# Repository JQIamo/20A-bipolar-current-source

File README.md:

# Bias Coils Current Controller
This repo provides information regarding the Bias Coils Current Controller (here on out referred to as “the controller”) used by the Schine Group at the Joint Quantum Institute (JQI) at University of Maryland, College Park. This is an experimental apparatus designed to drive Helmholtz coil pairs to cancel external magnetic fields which would otherwise disturb the experiment. The controller provides an output current proportional to an input voltage and features an ultra-low noise feedback circuit design for precise control of the output current down to the fractional mA level. The controller has three channels to independently control the magnetic fields along the x, y, and z axes.

## 20A-bipolar-current-source
This project is based on the [`20A-bipolar-current-source`](https://github.com/JQIamo/20A-bipolar-current-source/tree/faf83a785aa46d90d6e65fa55f9879bae6bd2d8a) design of Mingshu Zhao and Alessandro Restelli. Details on the circuit can be found in their [research article in AIP Advances](https://doi.org/10.1063/5.0138145).

## Circuit files
There are several KiCad project folders within the `kicad` directory in this repo.
* `controller_board` contains the circuit board for the main controller board on which the analog PI feedback is located.
* `Controller_supply` contains the controller's on-board power supply circuit board (used for powering the controller boards)
* `H-bridge` is for the development of the MOT coil current controller (empty project as of Jun 06, 2024).
* `rear` contains the original, liquid-cooled circuit board design housing the power MOSFETs that control the coil current. (Not used in this controller)
* `SchineLab_CoilFET_Board` contains the modified, air-cooled circuit board design housing the power MOSFETs for coil current control. (Used in this controller)

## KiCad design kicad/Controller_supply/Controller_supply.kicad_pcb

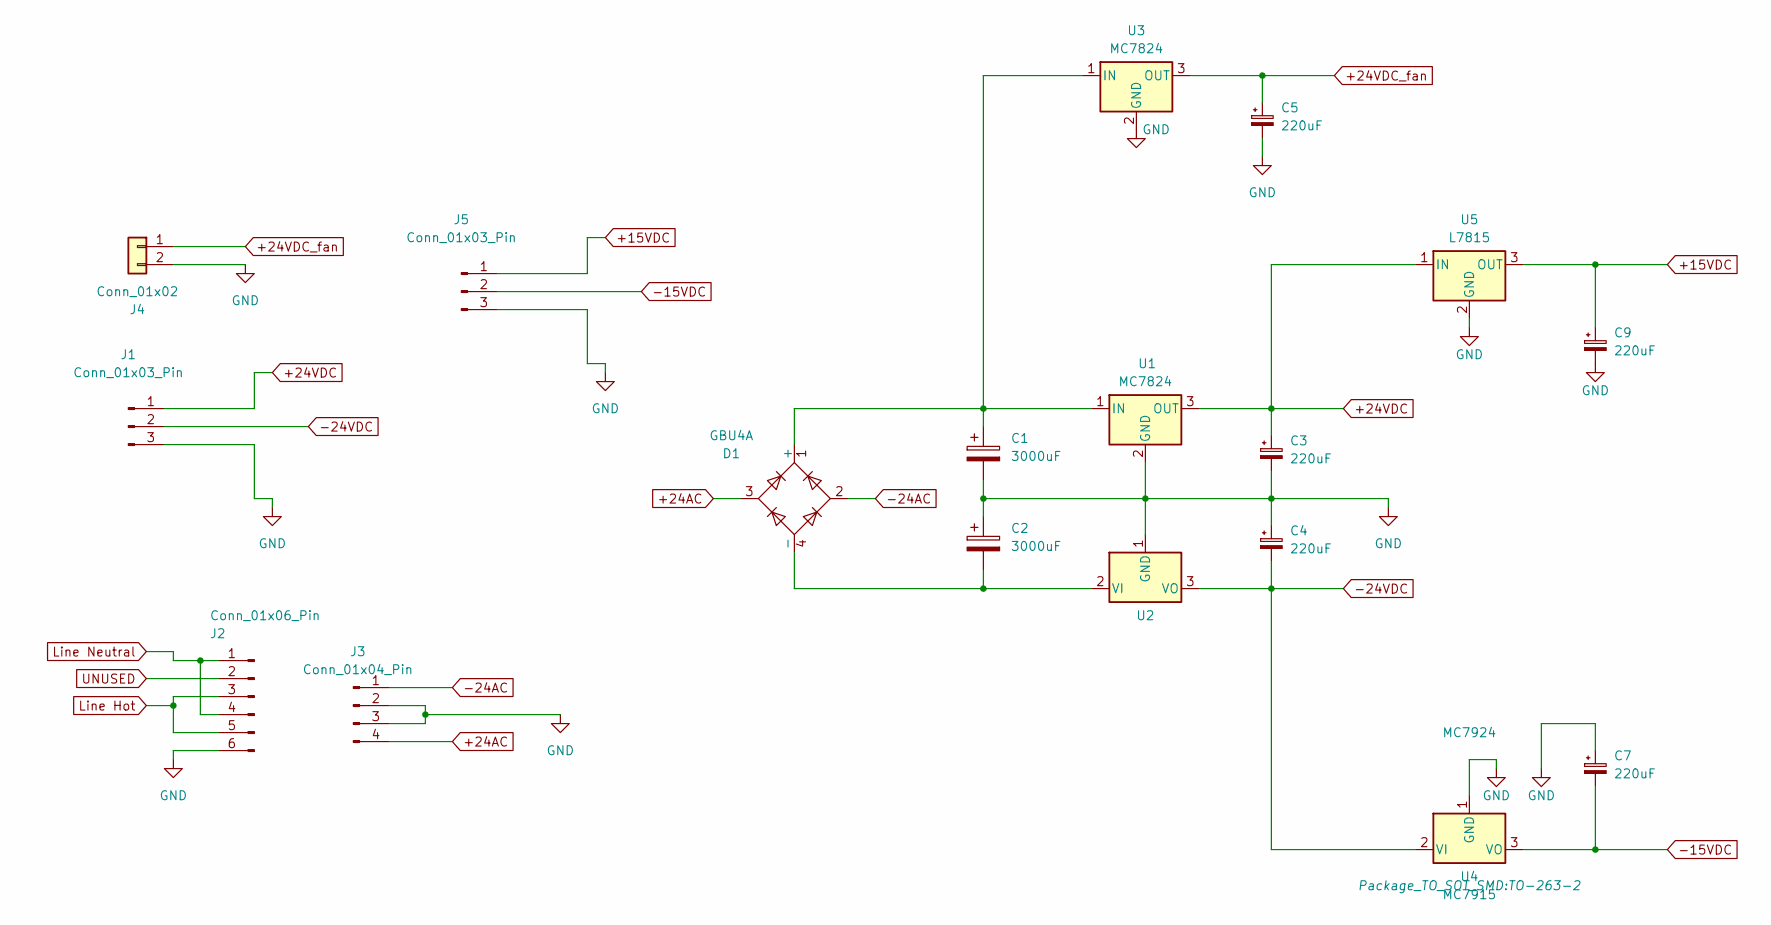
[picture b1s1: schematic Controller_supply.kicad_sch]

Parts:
C1, C2: 3000uF; CP_Elec_18x22; MPN EEE-FK1V302SV; DIGIKEY PARTNO P122523CT-ND
C3, C4, C5, C7, C9: 220uF; CP_Elec_10x10.5; MPN EEE-FK1H221P; DIGIKEY PARTNO PCE3812CT-ND
D1: GBU4A; Diode_Bridge_Vishay_GBU; MPN GBU4A; DIGIKEY PARTNO GBU4A-ND
J1, J5: Conn_01x03_Pin; PhoenixContact_GMSTBA_2,5_3-G-7,62_1x03_P7.62mm_Horizontal
J2: Conn_01x06_Pin
J3: Conn_01x04_Pin; Generic_pin-to-housing_1x04_P5.00mm_Horizontal
J4: Conn_01x02; Generic_7x7.5mm-footprt_1x02_P3.50mm_Horizontal
U1, U3: MC7824; TO-263-2; MPN MC7824CD2TR4G; DIGIKEY PARTNO MC7824CD2TR4GOSCT-ND
U2: MC7924; TO-263-2; MPN MC7924CD2TG; DIGIKEY PARTNO MC7924CD2TG-ND
U4: MC7915; TO-263-2
U5: L7815; TO-263-2

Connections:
+15VDC: C9.1, J5.1, U5.3 (OUT)
+24AC: D1.3, J3.4
+24VDC: C3.1, J1.1, U1.3 (OUT), U5.1 (IN)
+24VDC_fan: C5.1, J4.1, U3.3 (OUT)
-15VDC: C7.2, J5.2, U4.3 (VO)
-24AC: D1.2, J3.1
-24VDC: C4.2, J1.2, U2.3 (VO), U4.2 (VI)
GND: C1.2, C2.1, C3.2, C4.1, C5.2, C7.1, C9.2, J1.3, J2.6, J3.2, J3.3, J4.2, J5.3, U1.2 (GND), U2.1 (GND), U3.2 (GND), U4.1 (GND), U5.2 (GND)
unnamed: C1.1, D1.1 (+), U1.1 (IN), U3.1 (IN)
unnamed: C2.2, D1.4 (-), U2.2 (VI)
unnamed: J2.1, J2.4
unnamed: J2.3, J2.5

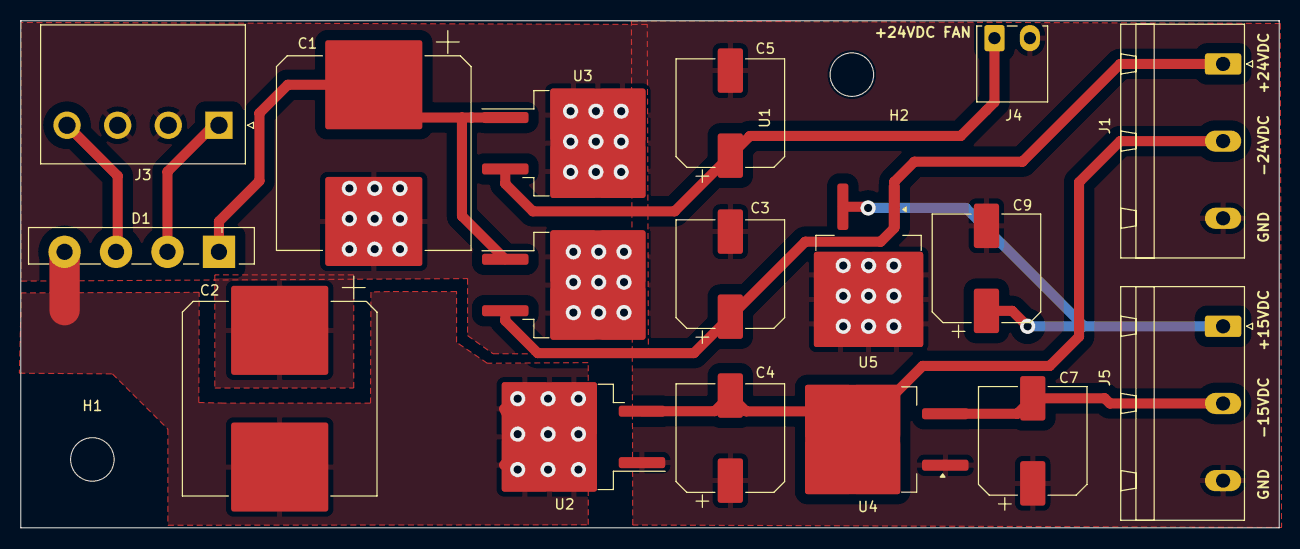
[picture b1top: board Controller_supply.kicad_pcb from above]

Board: 2 copper layers, 124.3 x 50.1 mm, 19 parts (0 on the bottom side), 10 nets.

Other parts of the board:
H1, H2: MountingHole_4.3mm_M4

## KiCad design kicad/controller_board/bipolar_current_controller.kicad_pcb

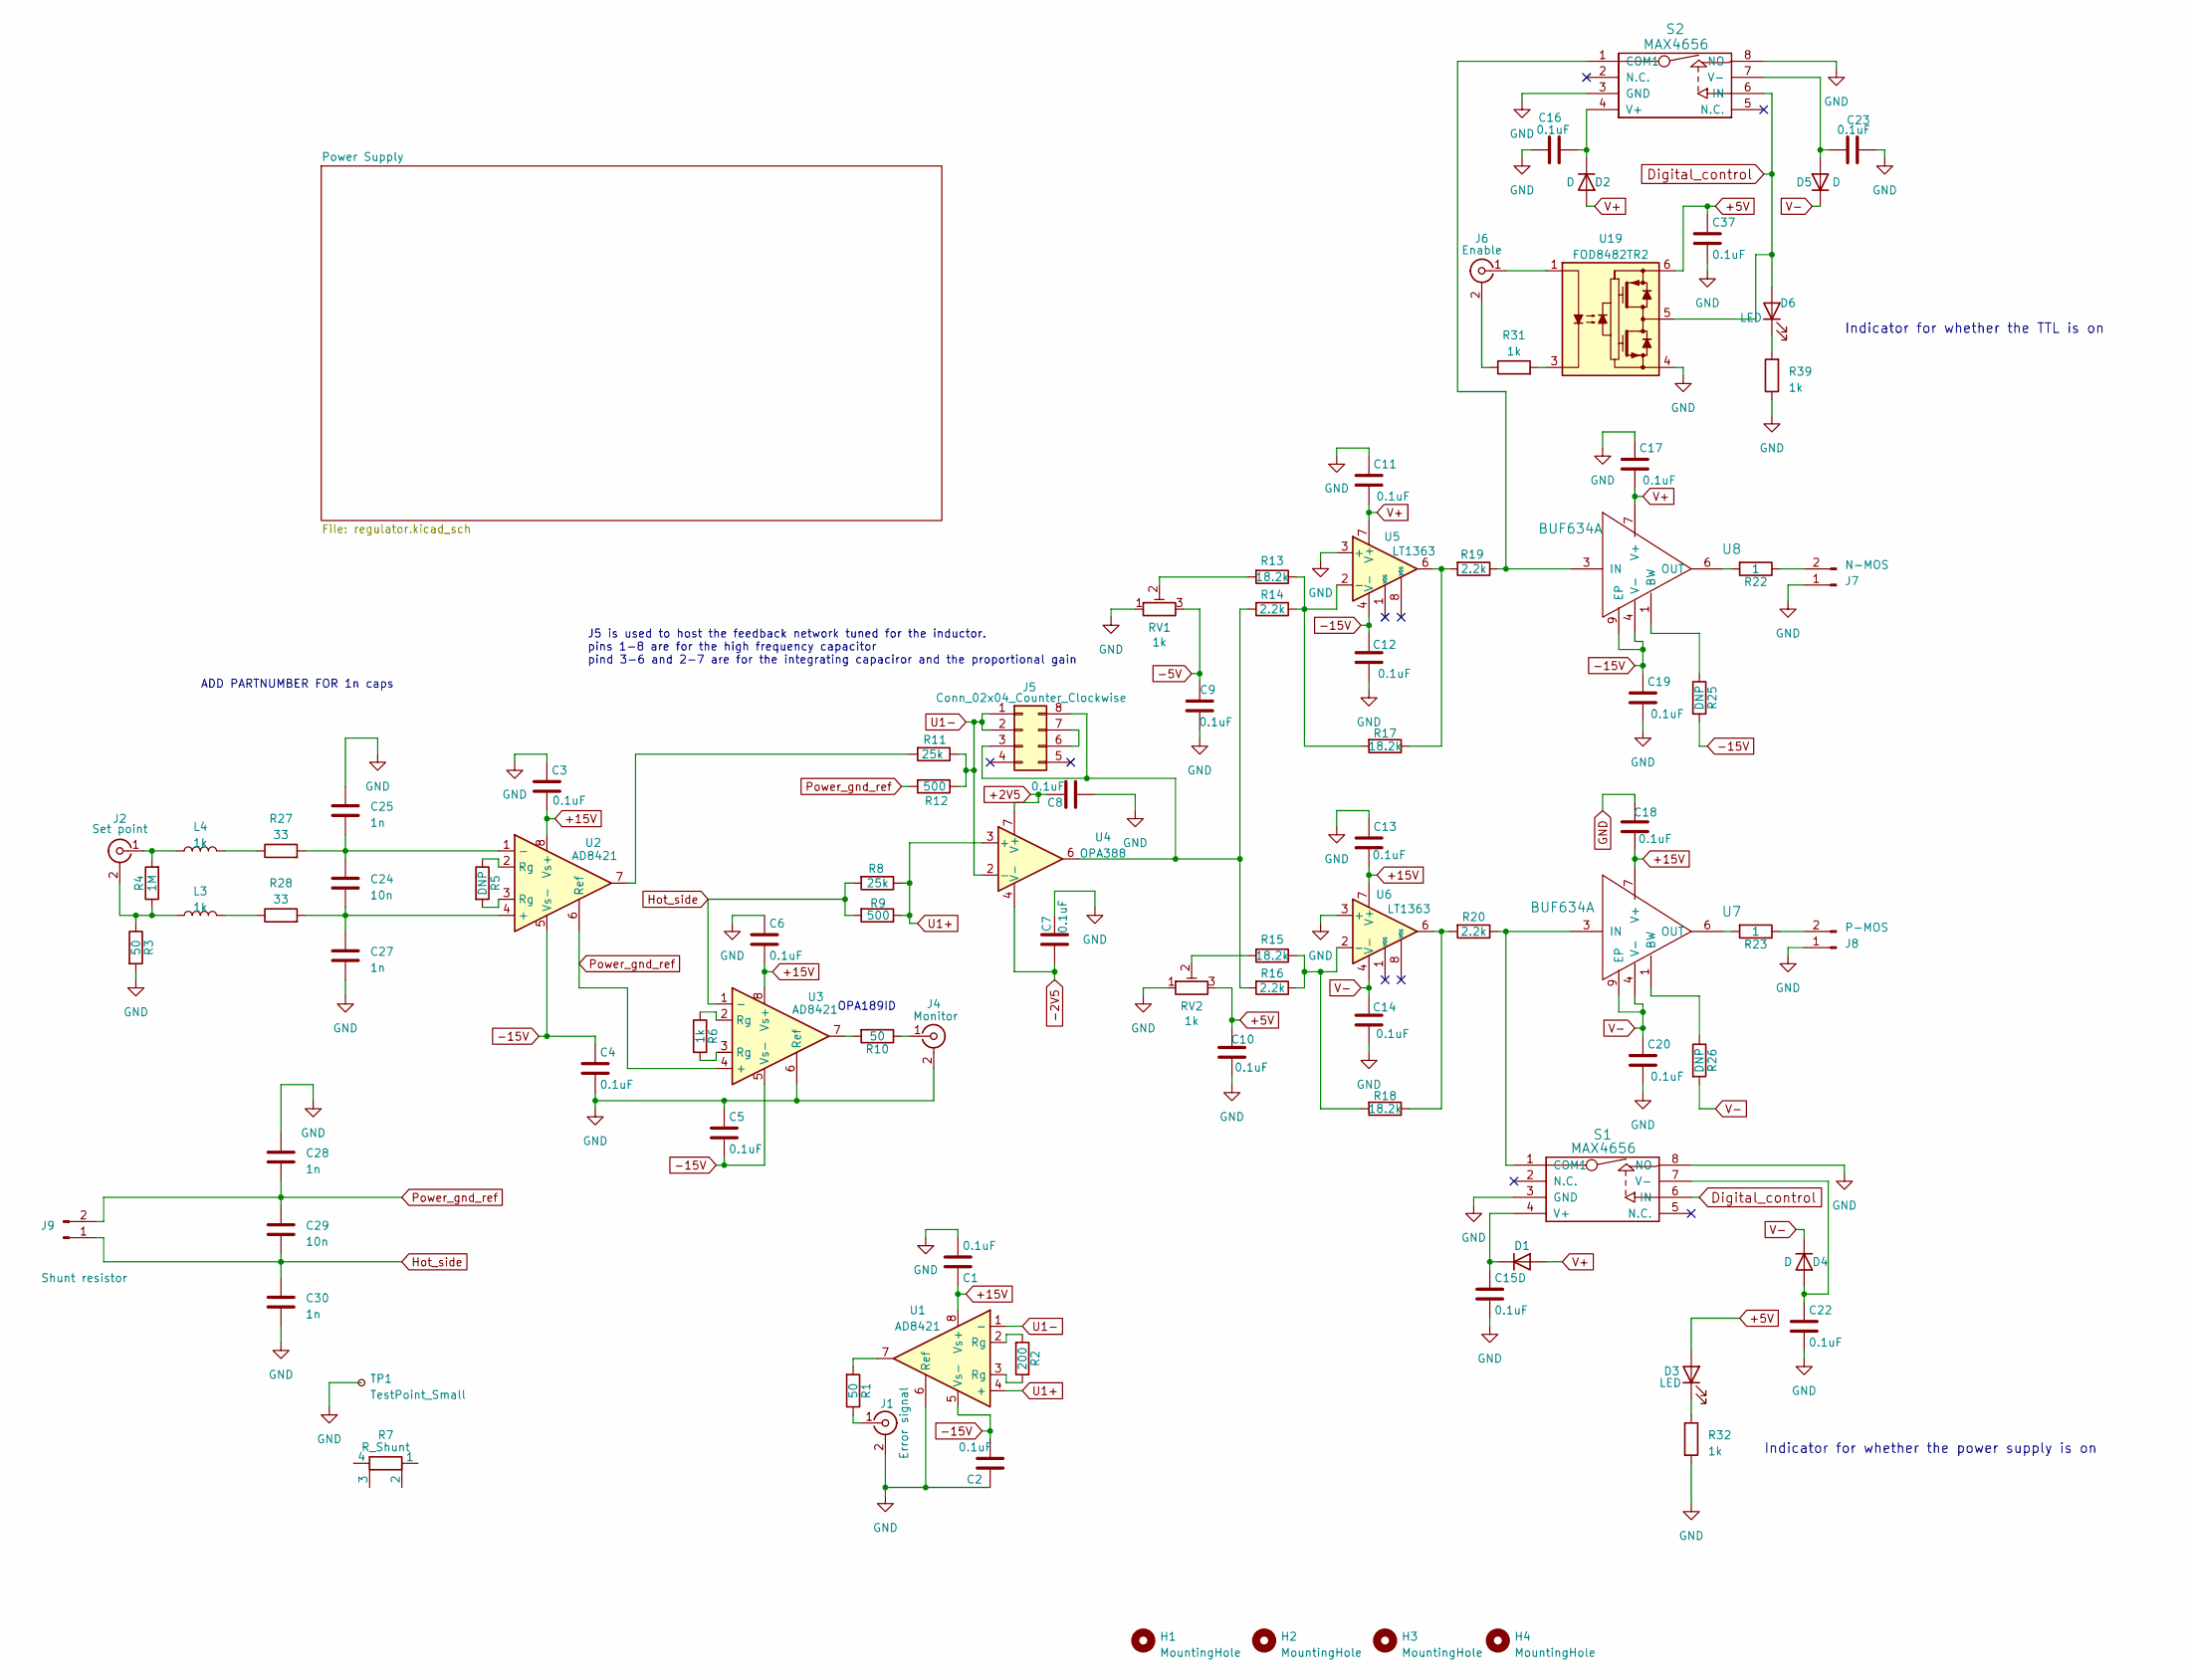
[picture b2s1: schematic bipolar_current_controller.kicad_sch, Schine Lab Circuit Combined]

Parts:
C1, C2, C3, C4, C5, C6, C7, C8, C9, C10, C11, C12, C13, C14, C15, C16, C17, C18, C19, C20, C22, C23, C37: 0.1uF; C_0603_1608Metric; MPN GCM188R71H104JA57D; DIGIKEY PARTNO 490-14357-1-ND
C24, C29: 10n; C_0603_1608Metric; MPN PARTNO C1608C0G1H103J080AA; DIGIKEY PARTNO 445-7404-1-ND
C25, C27, C28, C30: 1n; C_0603_1608Metric; MPN 1276-1018-1-ND; DIGIKEY PARTNO 1276-1018-1-ND
D1, D2, D4, D5: D; D_MiniMELF; MPN CLL4150 TR PBFREE; DIGIKEY PARTNO 1514-CLL4150TRPBFREECT-ND
D3, D6: LED; LED_D5.0mm_Horizontal_O3.81mm_Z3.0mm; MPN HLMP-4700-C0002; DIGIKEY PARTNO 516-2483-1-ND
H1, H2, H3, H4: MountingHole; MountingHole_4mm
J1: Error signal; BNC_Amphenol_B6252HB-NPP3G-50_Horizontal_mount_float; MPN 5227161-7; DIGIKEY PARTNO A32260-ND
J2: Set point; BNC_Amphenol_B6252HB-NPP3G-50_Horizontal_mount_float; MPN 5227161-7; DIGIKEY PARTNO A32260-ND
J4: Monitor; BNC_Amphenol_B6252HB-NPP3G-50_Horizontal_mount_float; MPN 5227161-7; DIGIKEY PARTNO A32260-ND
J5: Conn_02x04_Counter_Clockwise; SSO-8_7.62x10.1mm_P2.54mm_Clearance8mm; MPN 114-87-308-41-134161; DIGIKEY PARTNO 1212-1032-ND
J6: Enable; BNC_Amphenol_B6252HB-NPP3G-50_Horizontal_mount_float; MPN 5227161-7; DIGIKEY PARTNO A32260-ND
J7: N-MOS; Molex_KK-254_AE-6410-02A_1x02_P2.54mm_Vertical
J8: P-MOS; Molex_KK-254_AE-6410-02A_1x02_P2.54mm_Vertical
J9: Shunt resistor; Molex_KK-254_AE-6410-02A_1x02_P2.54mm_Vertical
L3, L4: 1k; L_0603_1608Metric; MPN MMZ1608R102ATA00; DIGIKEY PARTNO 445-MMZ1608R102ATA00CT-ND
R1, R3, R10: 50; R_0603_1608Metric; MPN FC0603E50R0BTBST1; DIGIKEY PARTNO 764-FC0603E50R0BTBST1CT-ND
R2: 200; R_0603_1608Metric; MPN RNCF0603TKY200R; DIGIKEY PARTNO RNCF0603TKY200RCT-ND
R4: 1M; R_0603_1608Metric; MPN RT0603BRD071ML; DIGIKEY PARTNO YAG4498CT-ND
R5: DNP; R_0805_2012Metric
R6: 1k; R_0805_2012Metric; MPN RNCF0805TKY1K00; DIGIKEY PARTNO RG2012V1.0KPCT-ND
R7: R_Shunt; MPN Y09430R01000F9L; DIGIKEY PARTNO 804-1050-ND
R8, R11: 25k; R_2512_6332Metric; MPN Y174525K0000T9R; DIGIKEY PARTNO 804-1122-1-ND
R9, R12: 500; R_2512_6332Metric; MPN Y1121500R000T9R; DIGIKEY PARTNO Y1121-500CT-ND
R13, R15, R17, R18: 18.2k; R_0805_2012Metric; MPN RK73H2ATTD1822F; DIGIKEY PARTNO 2019-RK73H2ATTD1822FCT-ND
R14, R16, R19, R20: 2.2k; R_0805_2012Metric; MPN MCU08050C2201FP500; DIGIKEY PARTNO 749-1728-1-ND
R22, R23: 1; R_0603_1608Metric; MPN RNCP0603FTD1R00; DIGIKEY PARTNO RNCP0603FTD1R00CT-ND
R25, R26: DNP; R_0603_1608Metric
R27, R28: 33; R_0603_1608Metric; MPN RC0603FR-0733RL; DIGIKEY PARTNO 311-33.0HRCT-ND
R31, R32, R39: 1k; R_0603_1608Metric; MPN RNCP0603FTD1K00; DIGIKEY PARTNO RNCP0603FTD1K00CT-ND
RV1, RV2: 1k; Potentiometer_Bourns_3296W_Vertical; MPN 3296W-1-102LF; DIGIKEY PARTNO 3296W-102LF-ND
S1, S2: MAX4656; MAX4656ESA+; MPN MAX4656ESA+; DIGIKEY PARTNO MAX4656ESA+-ND
TP1: TestPoint_Small; Laird_Technologies_BMI-S-210-F_44.00x30.50mm; MPN BMI-S-210-F and BMI-S-210-C; DIGIKEY PARTNO 903-1057-1-ND and 903-1020-ND
U1, U2, U3: AD8421; AD8421ARZ-R7; MPN AD8421ARZ-R7; DIGIKEY PARTNO AD8421ARZ-R7CT-ND
U4: OPA388; OPA388IDR; Partno MPN; DIGIKEY PARTNO 296-45348-1-ND
U5, U6: LT1363; LT1363CS8#TRPBF; MPN LT1363CS8#TRPBF; DIGIKEY PARTNO 505-LT1363CS8#TRPBFCT-ND
U7, U8: BUF634A; TI_SO-PowerPAD-8_ThermalVias; MPN BUF634AIDDAR; DIGIKEY PARTNO 296-BUF634AIDDARCT-ND
U19: FOD8482TR2; SSO-6_6.8x4.6mm_P1.27mm_Clearance8mm; MPN FOD8482TR2; DIGIKEY PARTNO 488-FOD8482TR2CT-ND

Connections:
+2V5: C8.2, U4.7 (V+); also elsewhere on the board
+5V: C10.2, C37.1, D3.2 (A), RV2.3, U19.6 (VCC); also elsewhere on the board
+15V: C1.1, C3.2, C6.2, C13.2, C18.2, U1.8 (Vs+), U2.8 (Vs+), U3.8 (Vs+), U6.7 (V+), U7.7 (V+); also elsewhere on the board
-2V5: C7.1, U4.4 (V-); also elsewhere on the board
-5V: C9.1, RV1.3; also elsewhere on the board
-15V: C2.2, C4.1, C5.2, C12.2, C19.1, R25.2, U1.5 (Vs-), U2.5 (Vs-), U3.5 (Vs-), U5.4 (V-), U8.4 (V-), U8.9 (EP); also elsewhere on the board
Digital_control: D6.2 (A), S1.6 (IN), S2.6 (IN), U19.5 (VO)
GND: C1.2, C2.1, C3.1, C4.2, C5.1, C6.1, C7.2, C8.1, C9.2, C10.1, C11.1, C12.1, C13.1, C14.1, C15.2, C16.1, C17.1, C18.1, C19.2, C20.2, C22.2, C23.1, C25.1, C27.2, C28.1, C30.2, C37.2, J1.2 (Ext), J4.2 (Ext), J7.1, J8.1, R3.2, R32.2, R39.1, RV1.1, RV2.1, S1.3 (GND), S1.8 (NO), S2.3 (GND), S2.8 (NO), TP1.1, U1.6 (Ref), U3.6 (Ref), U5.3 (+), U6.3 (+), U19.4 (VEE); also elsewhere on the board
Hot_side: C29.2, C30.1, J9.1, R8.2, R9.2, U3.1 (-)
unnamed: C15.1, D1.1 (K), S1.4 (V+)
unnamed: C16.2, D2.1 (K), S2.4 (V+)
unnamed: D3.1 (K), R32.1
unnamed: C22.1, D4.2 (A), S1.7 (V-)
unnamed: C23.2, D5.2 (A), S2.7 (V-)
unnamed: D6.1 (K), R39.2
unnamed: J1.1 (In), R1.1
unnamed: J2.2 (Ext), L3.1, R3.1, R4.1
unnamed: J2.1 (In), L4.1, R4.2
unnamed: J4.1 (In), R10.1
unnamed: J5.3, J5.8, R14.2, R16.2, U4.6
unnamed: J5.6, J5.7
unnamed: J6.2 (Ext), R31.1
unnamed: J6.1 (In), U19.1 (A)
unnamed: J7.2, R22.1
unnamed: J8.2, R23.1
unnamed: L3.2, R28.1
unnamed: L4.2, R27.1
unnamed: R1.2, U1.7
unnamed: R2.1, U1.3 (Rg)
unnamed: R2.2, U1.2 (Rg)
unnamed: R5.1, U2.2 (Rg)
unnamed: R5.2, U2.3 (Rg)
unnamed: R6.1, U3.2 (Rg)
unnamed: R6.2, U3.3 (Rg)
unnamed: R10.2, U3.7
unnamed: R11.2, U2.7
unnamed: R13.2, RV1.2
unnamed: R15.2, RV2.2
unnamed: R17.1, R19.2, U5.6
unnamed: R18.1, R20.2, U6.6
unnamed: R20.1, S1.1 (COM1), U7.3 (IN)
unnamed: R19.1, S2.1 (COM1), U8.3 (IN)
unnamed: C24.2, C27.1, R28.2, U2.4 (+)
unnamed: C24.1, C25.2, R27.2, U2.1 (-)
unnamed: R13.1, R14.1, R17.2, U5.2 (-)
unnamed: R15.1, R16.1, R18.2, U6.2 (-)
unnamed: R26.1, U7.1 (BW)
unnamed: R23.2, U7.6 (OUT)
unnamed: R25.1, U8.1 (BW)
unnamed: R22.2, U8.6 (OUT)
unnamed: R31.2, U19.3 (C)
Power_gnd_ref: C28.2, C29.1, J9.2, R12.2, U2.6 (Ref), U3.4 (+)
U1+: R8.1, R9.1, U1.4 (+), U4.3 (+)
U1-: J5.1, J5.2, R11.1, R12.1, U1.1 (-), U4.2 (-)
V+: C11.2, C17.2, D1.2 (A), D2.2 (A), U5.7 (V+), U8.7 (V+); also elsewhere on the board
V-: C14.2, C20.1, D4.1 (K), D5.1 (K), R26.2, U6.4 (V-), U7.4 (V-), U7.9 (EP); also elsewhere on the board

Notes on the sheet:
J5 is used to host the feedback network tuned for the inductor. pins 1-8 are for the high frequency capacitor pind 3-6 and 2-7 are for the integrating capaciror and the proportional gain
ADD PARTNUMBER FOR 1n caps
Indicator for whether the TTL is on
Indicator for whether the power supply is on
OPA189ID

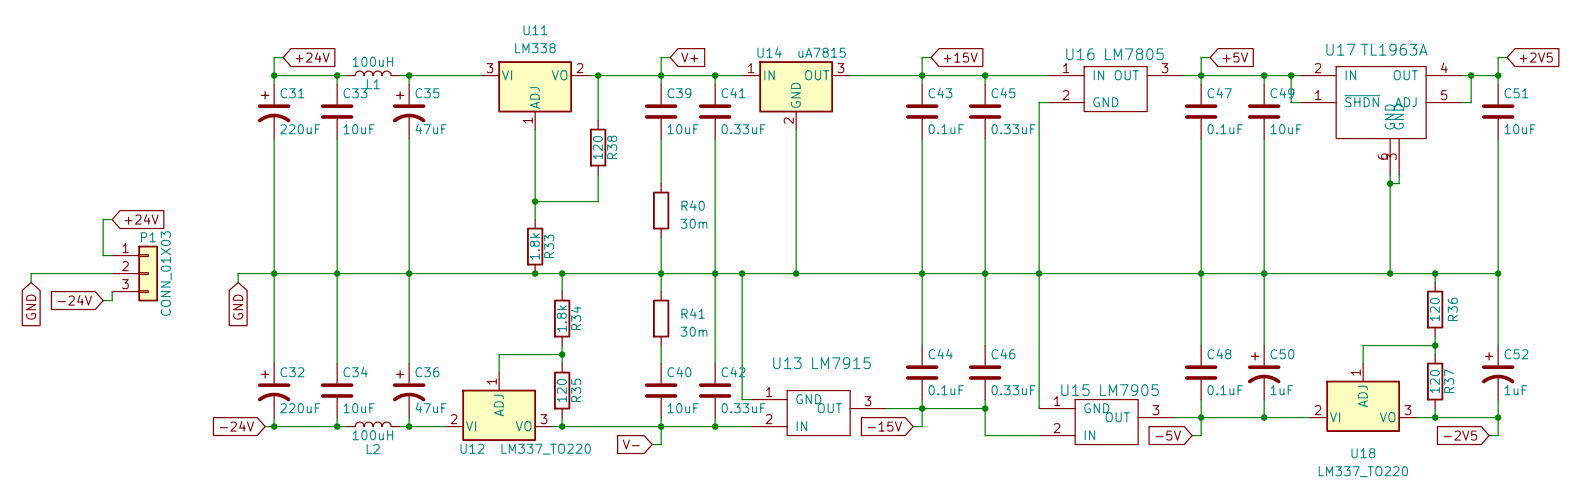
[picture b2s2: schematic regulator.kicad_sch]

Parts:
C31, C32: 220uF; CAP_polar_220uF; MPN EEE-FK1V221AP; DIGIKEY PARTNO PCE4428CT-ND
C33, C34, C39, C40, C49, C51: 10uF; C_1210_3225Metric; MPN C3225X7R1H106M250AC; DIGIKEY PARTNO 445-14933-1-ND
C35, C36: 47uF; CP_EIA-7343-43_Kemet-X; MPN T495X476K035ATE300; DIGIKEY PARTNO 399-3905-1-ND
C41, C42, C45, C46: 0.33uF; C_0603_1608Metric; MPN C1608X7R1H334K080AC; DIGIKEY PARTNO 445-5950-1-ND
C43, C44, C47, C48: 0.1uF; C_0603_1608Metric; MPN GCM188R71H104JA57D; DIGIKEY PARTNO 490-14357-1-ND
C50, C52: 1uF; CP_EIA-3528-21_Kemet-B; MPN T491B105K050AT; DIGIKEY PARTNO 399-9720-1-ND
L1, L2: 100uH; L_TDK_SLF10145; MPN SLF10145T-101M1R0-PF; DIGIKEY PARTNO 445-1976-1-ND
P1: CONN_01X03; Conn_01X03-3.5mm; MPN 1984620; DIGIKEY PARTNO 277-1722-ND
R33, R34: 1.8k; R_0603_1608Metric; MPN PTN0603E1801BST1; DIGIKEY PARTNO 764-1393-1-ND
R35, R36, R37, R38: 120; R_0603_1608Metric; MPN RG1608P-121-B-T5; DIGIKEY PARTNO RG16P120BCT-ND
R40, R41: 30m; R_1206_3216Metric; MPN D1WEL1206MR033F-T5; DIGIKEY PARTNO 4463-D1WEL1206MR033F-T5CT-ND
U11: LM338; TO-220-3_Vertical; MPN LM338T/NOPB; DIGIKEY PARTNO LM338T/NOPB-ND
U12: LM337_TO220; TO-220-3_Vertical; MPN LM337SP; DIGIKEY PARTNO 497-1585-5-ND
U13: LM7915; TO-263-2; MPN MC7915ACD2TG; DIGIKEY PARTNO MC7915ACD2TGOS-ND
U14: uA7815; TO-252-2; MPN BA7815FP-E2; DIGIKEY PARTNO BA7815FP-E2CT-ND
U15: LM7905; TO-263-2; MPN L7905CD2T-TR; DIGIKEY PARTNO 497-1214-1-ND
U16: LM7805; TO-263-3_TabPin2; MPN UA7805CKTTR; DIGIKEY PARTNO 296-20796-1-ND
U17: TL1963A; TL1963ADCQR; MPN TL1963ADCQR; DIGIKEY PARTNO 296-25119-1-ND
U18: LM337_TO220; TO-263-3_TabPin2; MPN LM337KTTR; DIGIKEY PARTNO 296-20746-1-ND

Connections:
+2V5: C51.1, U17.4 (OUT), U17.5 (ADJ); also elsewhere on the board
+5V: C47.1, C49.1, U16.3 (OUT), U17.1 (~SHDN), U17.2 (IN); also elsewhere on the board
+15V: C43.1, C45.1, U14.3 (OUT), U16.1 (IN); also elsewhere on the board
+24V: C31.1, C33.1, L1.1, P1.1
-2V5: C52.2, R37.2, U18.3 (VO); also elsewhere on the board
-5V: C48.2, C50.2, U15.3 (OUT), U18.2 (VI); also elsewhere on the board
-15V: C44.2, C46.2, U13.3 (OUT), U15.2 (IN); also elsewhere on the board
-24V: C32.2, C34.2, L2.1, P1.3
GND: C31.2, C32.1, C33.2, C34.1, C35.2, C36.1, C41.2, C42.1, C43.2, C44.1, C45.2, C46.1, C47.2, C48.1, C49.2, C50.1, C51.2, C52.1, P1.2, R33.2, R34.1, R36.1, R40.2, R41.1, U13.1 (GND), U14.2 (GND), U15.1 (GND), U16.2 (GND), U17.3 (GND), U17.6 (GND); also elsewhere on the board
unnamed: C39.2, R40.1
unnamed: C40.1, R41.2
unnamed: R33.1, R38.2, U11.1 (ADJ)
unnamed: C35.1, L1.2, U11.3 (VI)
unnamed: R34.2, R35.1, U12.1 (ADJ)
unnamed: C36.2, L2.2, U12.2 (VI)
unnamed: R36.2, R37.1, U18.1 (ADJ)
V+: C39.1, C41.1, R38.1, U11.2 (VO), U14.1 (IN); also elsewhere on the board
V-: C40.2, C42.2, R35.2, U12.3 (VO), U13.2 (IN); also elsewhere on the board

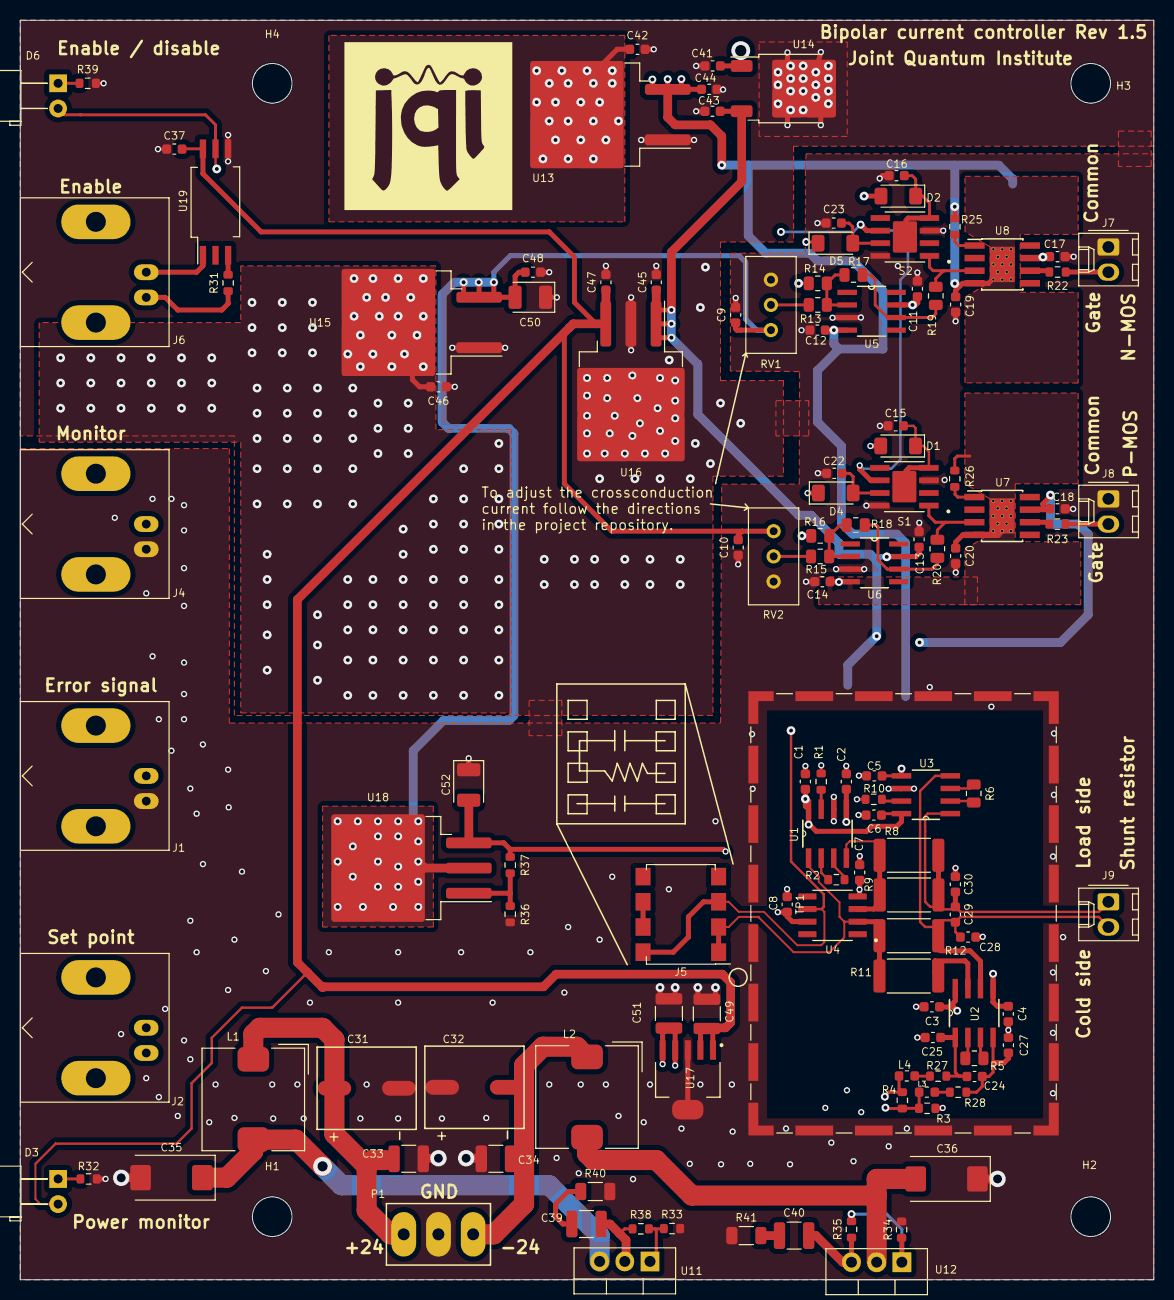
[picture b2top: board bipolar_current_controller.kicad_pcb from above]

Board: 4 copper layers, 114.3 x 127.0 mm, 130 parts (0 on the bottom side), 65 nets.

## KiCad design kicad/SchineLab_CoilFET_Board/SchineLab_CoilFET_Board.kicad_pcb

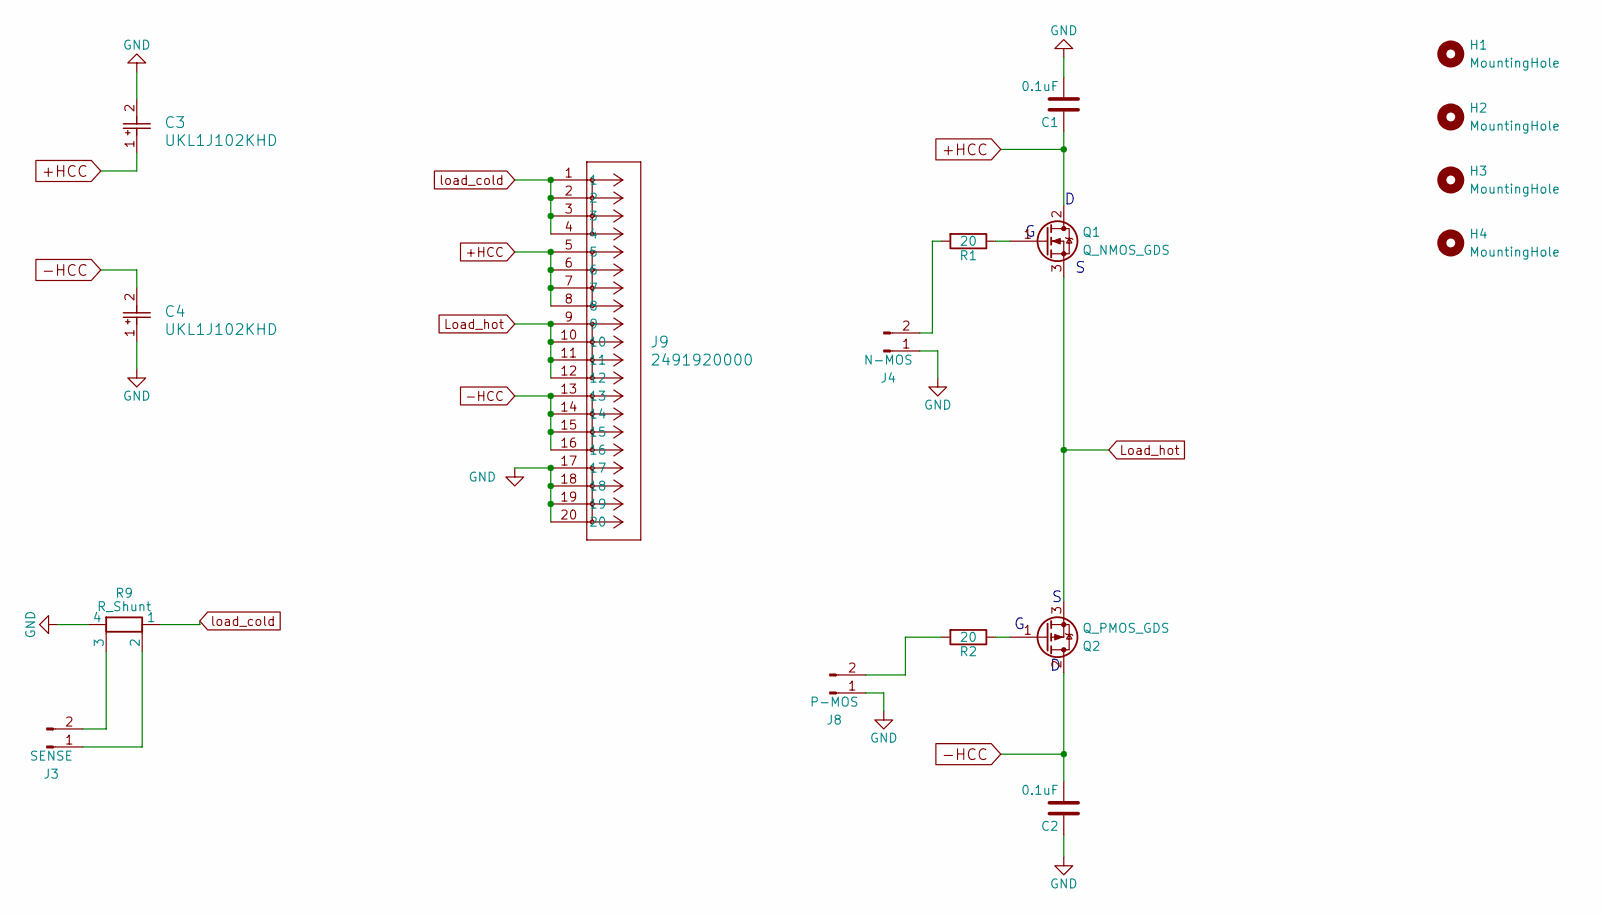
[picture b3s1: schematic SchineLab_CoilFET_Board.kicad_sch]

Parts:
C1, C2: 0.1uF; C_0603_1608Metric; MPN C0603C104J5RACAUTO; DIGIKEY PARTNO 399-6853-1-ND
C3, C4: UKL1J102KHD; CAP_UBY_18X35P5_NCH
H1, H2, H3, H4: MountingHole; MountingHole_4mm
J3: SENSE; PinHeader_1x02_P2.54mm_Vertical
J4: N-MOS; PinHeader_1x02_P2.54mm_Vertical
J8: P-MOS; PinHeader_1x02_P2.54mm_Vertical
J9: 2491920000; CONN_249192
Q1: Q_NMOS_GDS; PowerMOS; DIGIKEY PARTNO IXFN520N075T2-ND
Q2: Q_PMOS_GDS; PowerMOS; DIGIKEY PARTNO IXTN170P10P-ND
R1, R2: 20; R_0603_1608Metric_Pad0.98x0.95mm_HandSolder; DIGIKEY PARTNO P20.00BYCT-ND
R9: R_Shunt; SIP-4-ShuntResistor-Riedon

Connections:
+HCC: C1.1, C3.1, J9.5, J9.6, J9.7, J9.8, Q1.2 (D)
-HCC: C2.2, C4.2, J9.13, J9.14, J9.15, J9.16, Q2.2 (D)
GND: C1.2, C2.1, C3.2, C4.1, J4.1, J8.1, J9.17, J9.18, J9.19, J9.20, R9.4
Load_hot: J9.9, J9.10, J9.11, J9.12, Q1.3 (S), Q2.3 (S)
unnamed: J3.1, R9.2
unnamed: J3.2, R9.3
unnamed: J4.2, R1.2
unnamed: J8.2, R2.2
unnamed: Q1.1 (G), R1.1
unnamed: Q2.1 (G), R2.1
load_cold: J9.1, J9.2, J9.3, J9.4, R9.1

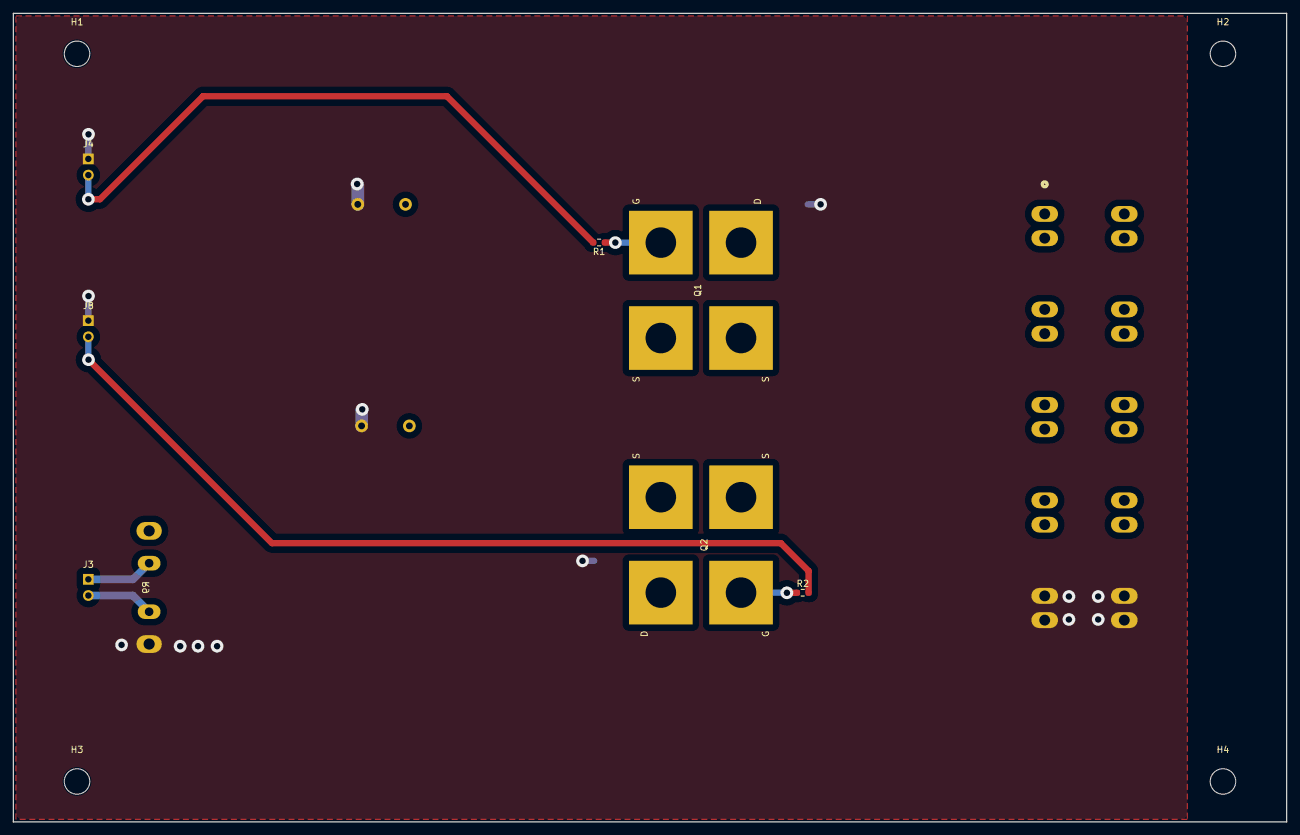
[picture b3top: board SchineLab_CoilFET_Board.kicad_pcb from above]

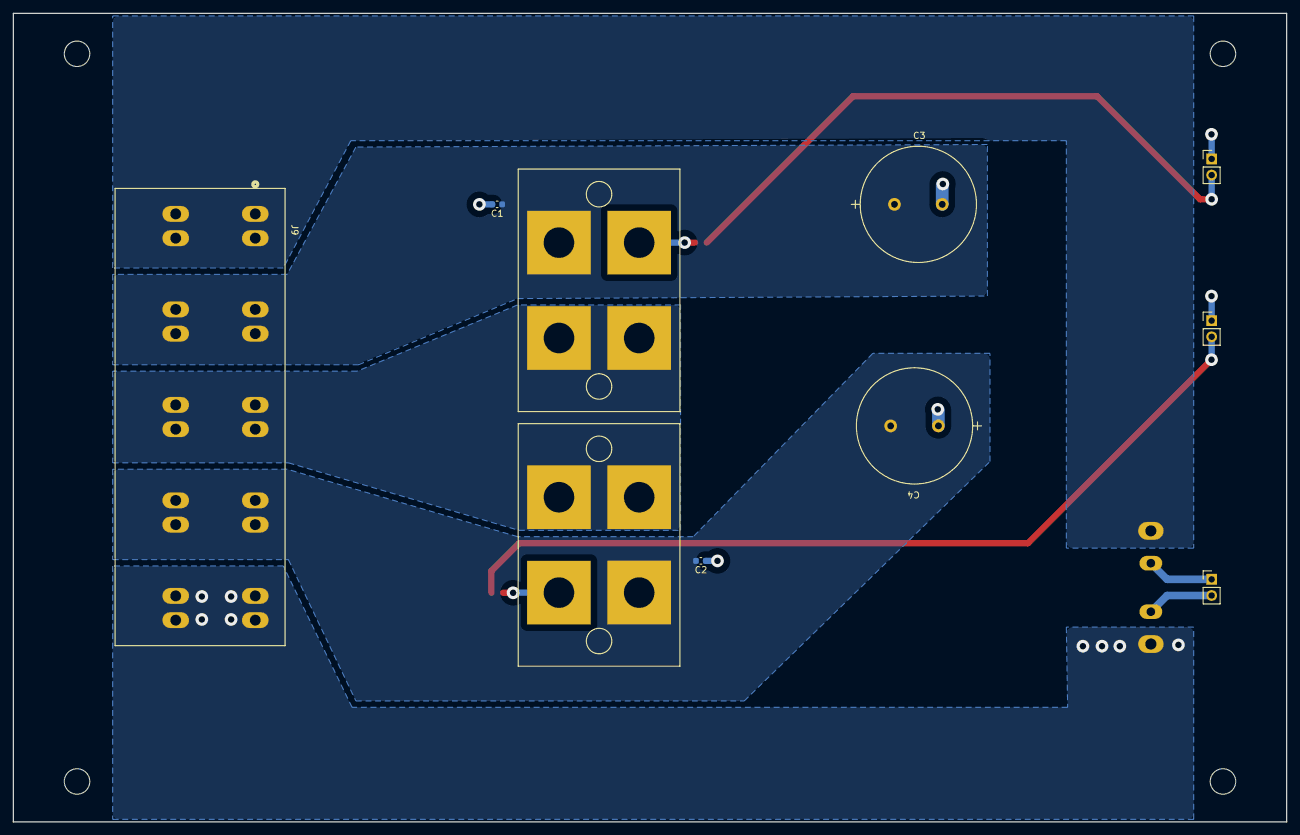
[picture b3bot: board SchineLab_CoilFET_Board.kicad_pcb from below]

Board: 2 copper layers, 200.0 x 127.0 mm, 17 parts (11 on the bottom side), 11 nets.
